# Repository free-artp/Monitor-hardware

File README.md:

It's a hardware project (Eagle) for small controller for woods factory by the ATMEGA328P.
1. Control the state (on/off) the big sawmill
2. Count the number of piece of wood
3. Report by network

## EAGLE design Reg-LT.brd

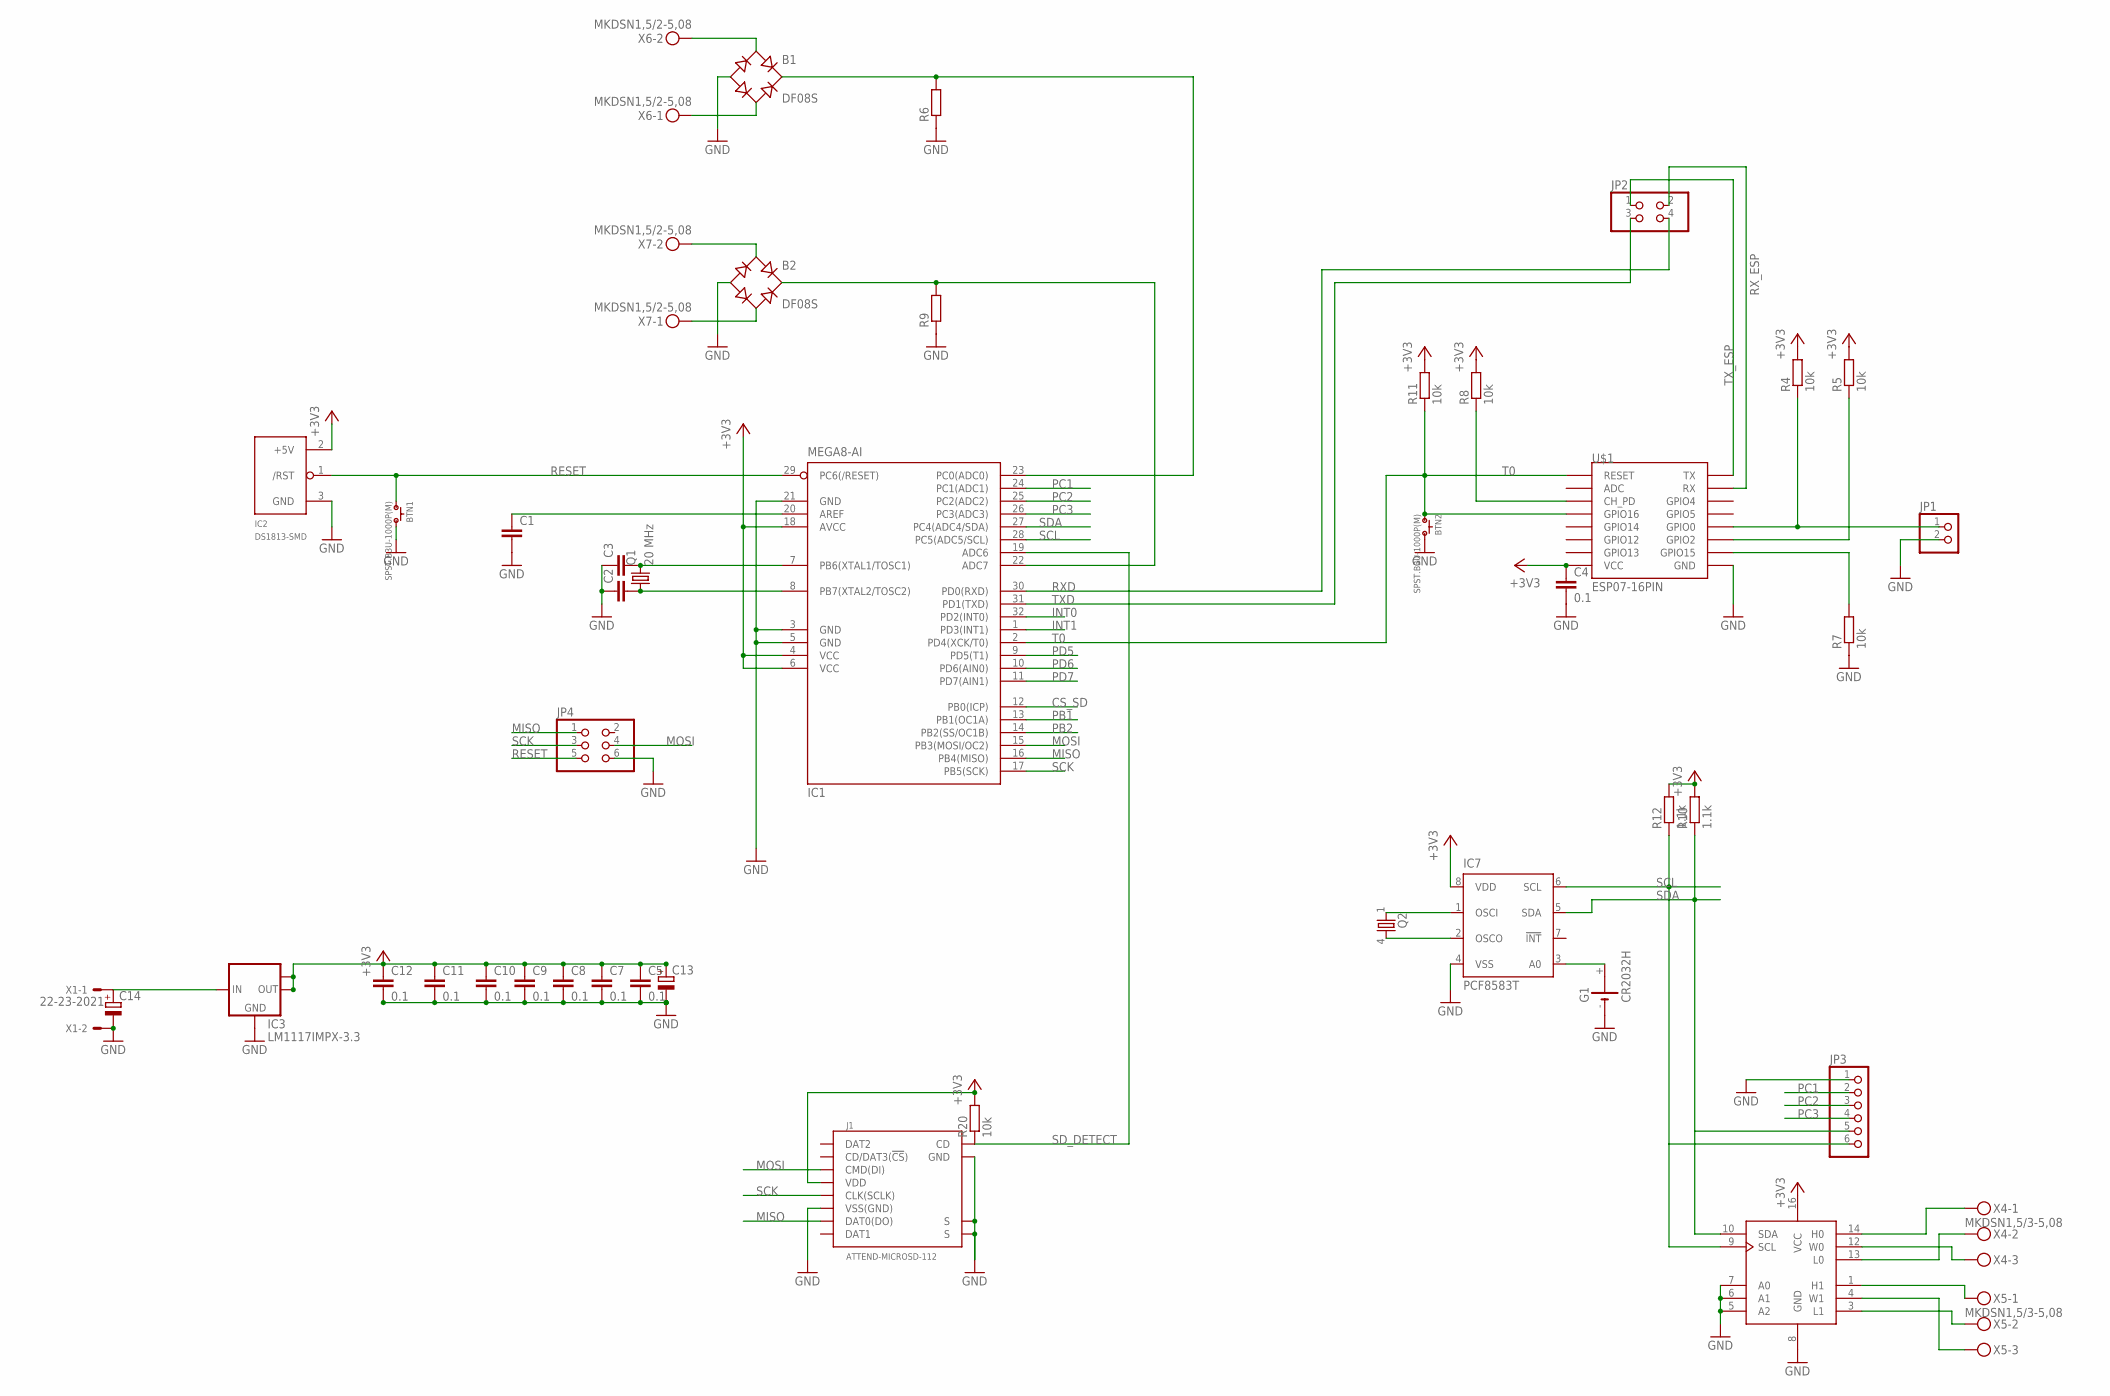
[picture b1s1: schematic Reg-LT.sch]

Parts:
B1, B2: DF08S; DFS
BTN1, BTN2: SPST.B3U-1000P(M); B3U-1000P(M)
C1: C-EUC0805K; C0805K
C2, C3: C-EUC0805; C0805
C4, C5, C7, C8, C9, C10, C11, C12: 0.1; C0805
C13, C14: CPOL-EU153CLV-0605; 153CLV-0605
G1: CR2032H
IC1: MEGA8-AI; TQFP32-08
IC2: DS1813-SMD; SOT-23
IC3: LM1117IMPX-3.3; SOT223
IC7: PCF8583T; SO8-7_5
J1: ATTEND-MICROSD-112; ATTEND-112
JP1: PINHD-1X2; 1X02
JP2: PINHD-2X2; 2X02
JP3: PINHD-1X6; 1X06
JP4: PINHD-2X3; 2X03
Q1: 20 MHz; SM49
Q2: MA306
R4, R5, R7, R8, R11, R20: 10k; R0805
R6, R9: R-EU_VMTA55; VMTA55
R10, R12: 1.1k; R0805
U$1: ESP07-16PIN
U$5: DS1803ZSO16; SO16
X1: 22-23-2021
X4, X5: MKDSN1,5/3-5,08
X6, X7: MKDSN1,5/2-5,08

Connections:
+3V3: C4.1, C5.1, C7.1, C8.1, C9.1, C10.1, C11.1, C12.1, C13.+, IC1.4 (VCC), IC1.6 (VCC), IC1.18 (AVCC), IC2.2 (+5V), IC3.2 (OUT), IC3.TAB (OUT1), IC7.8 (VDD), J1.VDD, R4.2, R5.2, R8.2, R10.2, R11.2, R12.2, R20.2, U$1.VCC, U$5.16 (VCC)
CS_SD: IC1.12 (PB0(ICP))
GND: B1.-, B2.-, BTN1.2, BTN2.2, C1.2, C2.1, C3.1, C4.2, C5.2, C7.2, C8.2, C9.2, C10.2, C11.2, C12.2, C13.-, C14.-, G1.-, IC1.3 (GND), IC1.5 (GND), IC1.21 (GND), IC2.3 (GND), IC3.1 (GND), IC7.4 (VSS), J1.GND, J1.S1 (S), J1.S2 (S), J1.VSS (VSS(GND)), JP1.2, JP3.1, JP4.6, R6.1, R7.1, R9.1, U$1.GND, U$5.5 (A2), U$5.6 (A1), U$5.7 (A0), U$5.8 (GND), X1.2
INT0: IC1.32 (PD2(INT0))
INT1: IC1.1 (PD3(INT1))
MISO: IC1.16 (PB4(MISO)), J1.DAT0 (DAT0(DO)), JP4.1
MOSI: IC1.15 (PB3(MOSI/OC2)), J1.CMD (CMD(DI)), JP4.4
unnamed: B2.AC1, X7.2
unnamed: C1.1, IC1.20 (AREF)
unnamed: C3.2, IC1.7 (PB6(XTAL1/TOSC1)), Q1.2
unnamed: C2.2, IC1.8 (PB7(XTAL2/TOSC2)), Q1.1
unnamed: B2.AC2, X7.1
unnamed: B2.+, IC1.22 (ADC7), R9.2
unnamed: B1.AC2, X6.1
unnamed: JP1.1, R4.1, U$1.GPIO0
unnamed: R5.1, U$1.GPIO2
unnamed: R7.2, U$1.GPIO15
unnamed: R8.1, U$1.CH_PD
unnamed: B1.AC1, X6.2
unnamed: IC7.1 (OSCI), Q2.1
unnamed: IC7.2 (OSCO), Q2.4 (2)
unnamed: U$5.13 (L0), X4.2
unnamed: U$5.12 (W0), X4.3
unnamed: B1.+, IC1.23 (PC0(ADC0)), R6.2
unnamed: U$5.14 (H0), X4.1
unnamed: U$5.1 (H1), X5.1
unnamed: U$5.3 (L1), X5.2
unnamed: U$5.4 (W1), X5.3
unnamed: G1.+, IC7.3 (A0)
PB1: IC1.13 (PB1(OC1A))
PB2: IC1.14 (PB2(SS/OC1B))
PC1: IC1.24 (PC1(ADC1)), JP3.2
PC2: IC1.25 (PC2(ADC2)), JP3.3
PC3: IC1.26 (PC3(ADC3)), JP3.4
PD5: IC1.9 (PD5(T1))
PD6: IC1.10 (PD6(AIN0))
PD7: IC1.11 (PD7(AIN1))
PW: C14.+, IC3.3 (IN), X1.1
RESET: BTN1.1, IC1.29 (PC6(/RESET)), IC2.1 (/RST), JP4.5
RXD: IC1.30 (PD0(RXD)), JP2.4
RX_ESP: JP2.2, U$1.RX
SCK: IC1.17 (PB5(SCK)), J1.CLK (CLK(SCLK)), JP4.3
SCL: IC1.28 (PC5(ADC5/SCL)), IC7.6 (SCL), JP3.6, R12.1, U$5.9 (SCL)
SDA: IC1.27 (PC4(ADC4/SDA)), IC7.5 (SDA), JP3.5, R10.1, U$5.10 (SDA)
SD_DETECT: IC1.19 (ADC6), J1.CD, R20.1
T0: BTN2.1, IC1.2 (PD4(XCK/T0)), R11.1, U$1.GPIO16, U$1.REST (RESET)
TXD: IC1.31 (PD1(TXD)), JP2.3
TX_ESP: JP2.1, U$1.TX

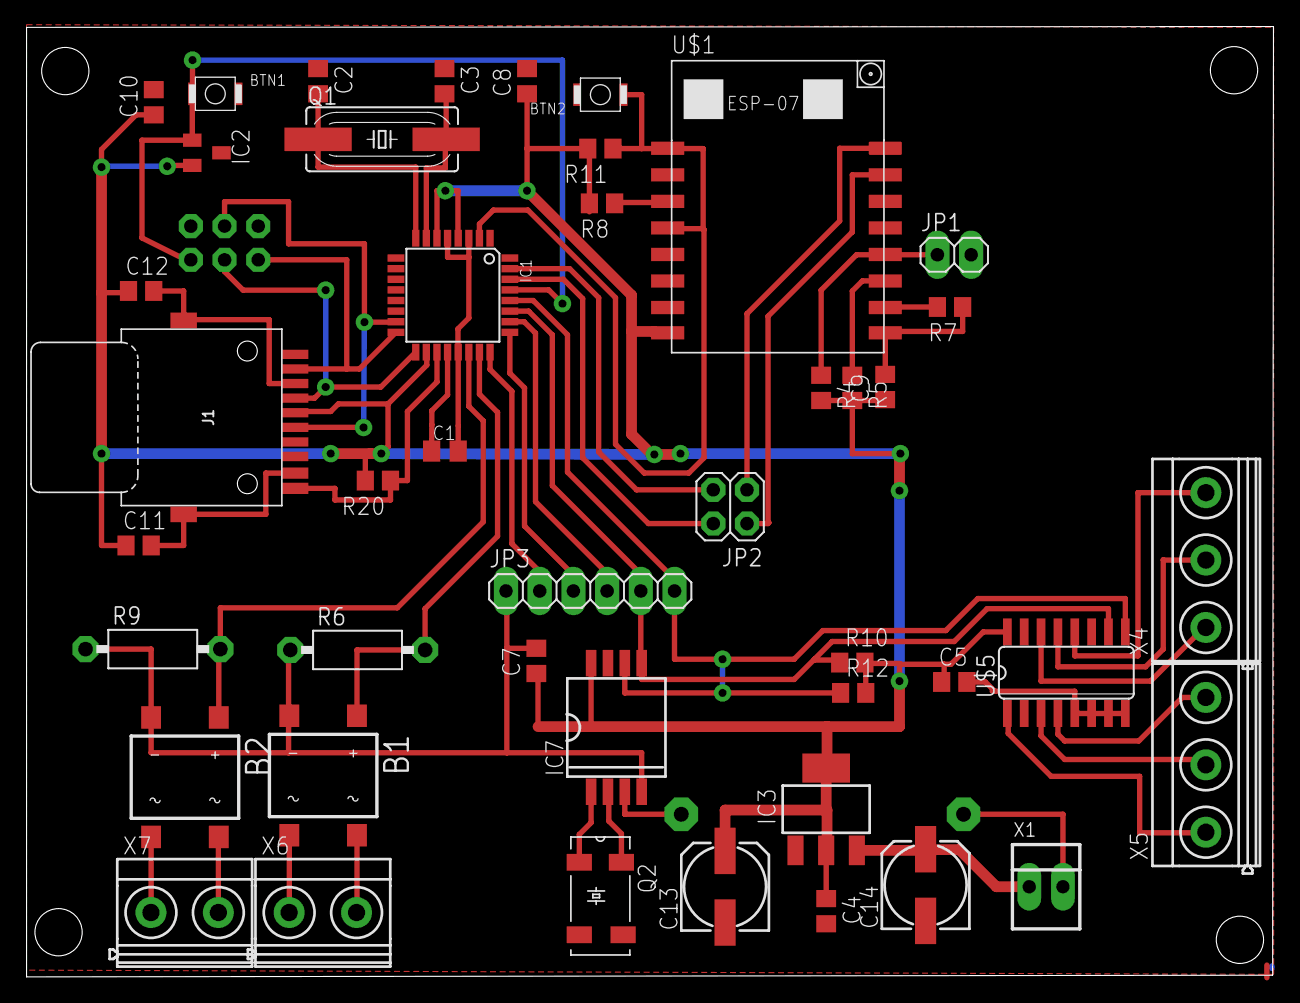
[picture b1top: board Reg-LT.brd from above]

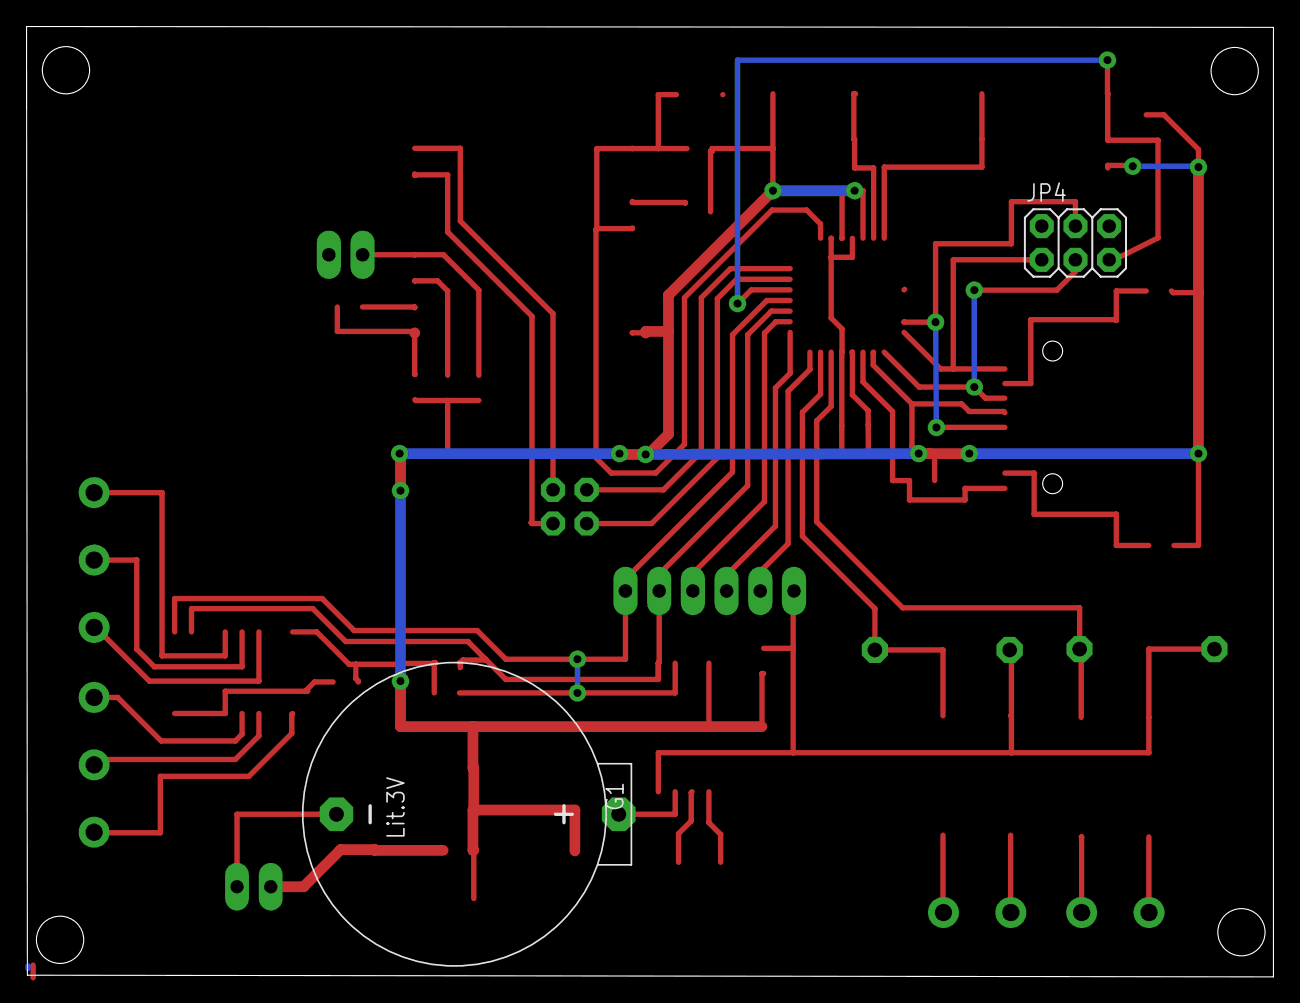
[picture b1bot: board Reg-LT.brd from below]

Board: 2 copper layers, 94.0 x 71.6 mm, 46 parts (2 on the bottom side), 40 nets.

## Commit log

2016-11-02 sd-card no-module
2016-11-06 timer - no-module
2016-11-13 no amplifires
2016-12-11 Readme
2016-12-14 input-rectifier
